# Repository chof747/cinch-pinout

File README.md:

# Cinch pinout board

This is a simple pinout board which enables to use a cinch plug on a breadboard.

## Used parts:

- **MJ-2509N:MJ-2509N**: The cinch plug for PHT mounting
- **3-Pin 2.54mm Pinheader**: To connect to the breadboard
- **1k Resistor**: A either a 0603 surface mount or a throughhole resistor to enable the voltage divider

## Revision History

- **v1.0**: Base version (filed for fabrication: 19.11.2022; first successfull assembly: 25.11.2022)
- **v1.1**: Changed resistor footprints to enable either an SMD or a Throughole resistor (filed for fabrication: 04.12.2022)

## Todos

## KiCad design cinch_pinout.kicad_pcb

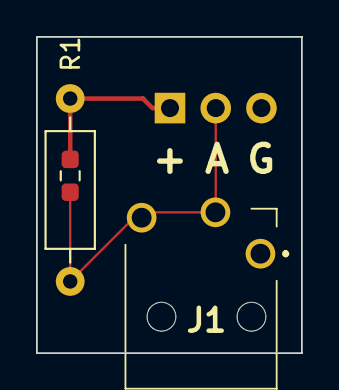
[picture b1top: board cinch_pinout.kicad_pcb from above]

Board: 2 copper layers, 14.7 x 17.6 mm, 4 parts (1 on the bottom side), 3 nets.

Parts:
J1: Conn; MJ2509N
J2: Pinout; PinHeader_1x03_P2.54mm_Vertical
R1: 1k; R_0603_1608Metric_Pad0.98x0.95mm_HandSolder
R1T1: 1k; R_Axial_DIN0207_L6.3mm_D2.5mm_P10.16mm_Horizontal

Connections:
+3V3: J2.1, R1.1, R1T1.1
AIN: J1.2, J1.3, J2.2, R1.2, R1T1.2
GND: J1.1, J2.3

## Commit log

2022-11-22 Initial revision
    - Filed for fabrication on 19.11.2022
2022-11-22 Changed resistor footprint
    Enables now both: SMD or throughhole resistor
2022-12-04 Revision 1: Added footprint for THP resistor
    - Added footprint
    - Updated Readme
2023-04-27 Updated template for KiCAD 7
